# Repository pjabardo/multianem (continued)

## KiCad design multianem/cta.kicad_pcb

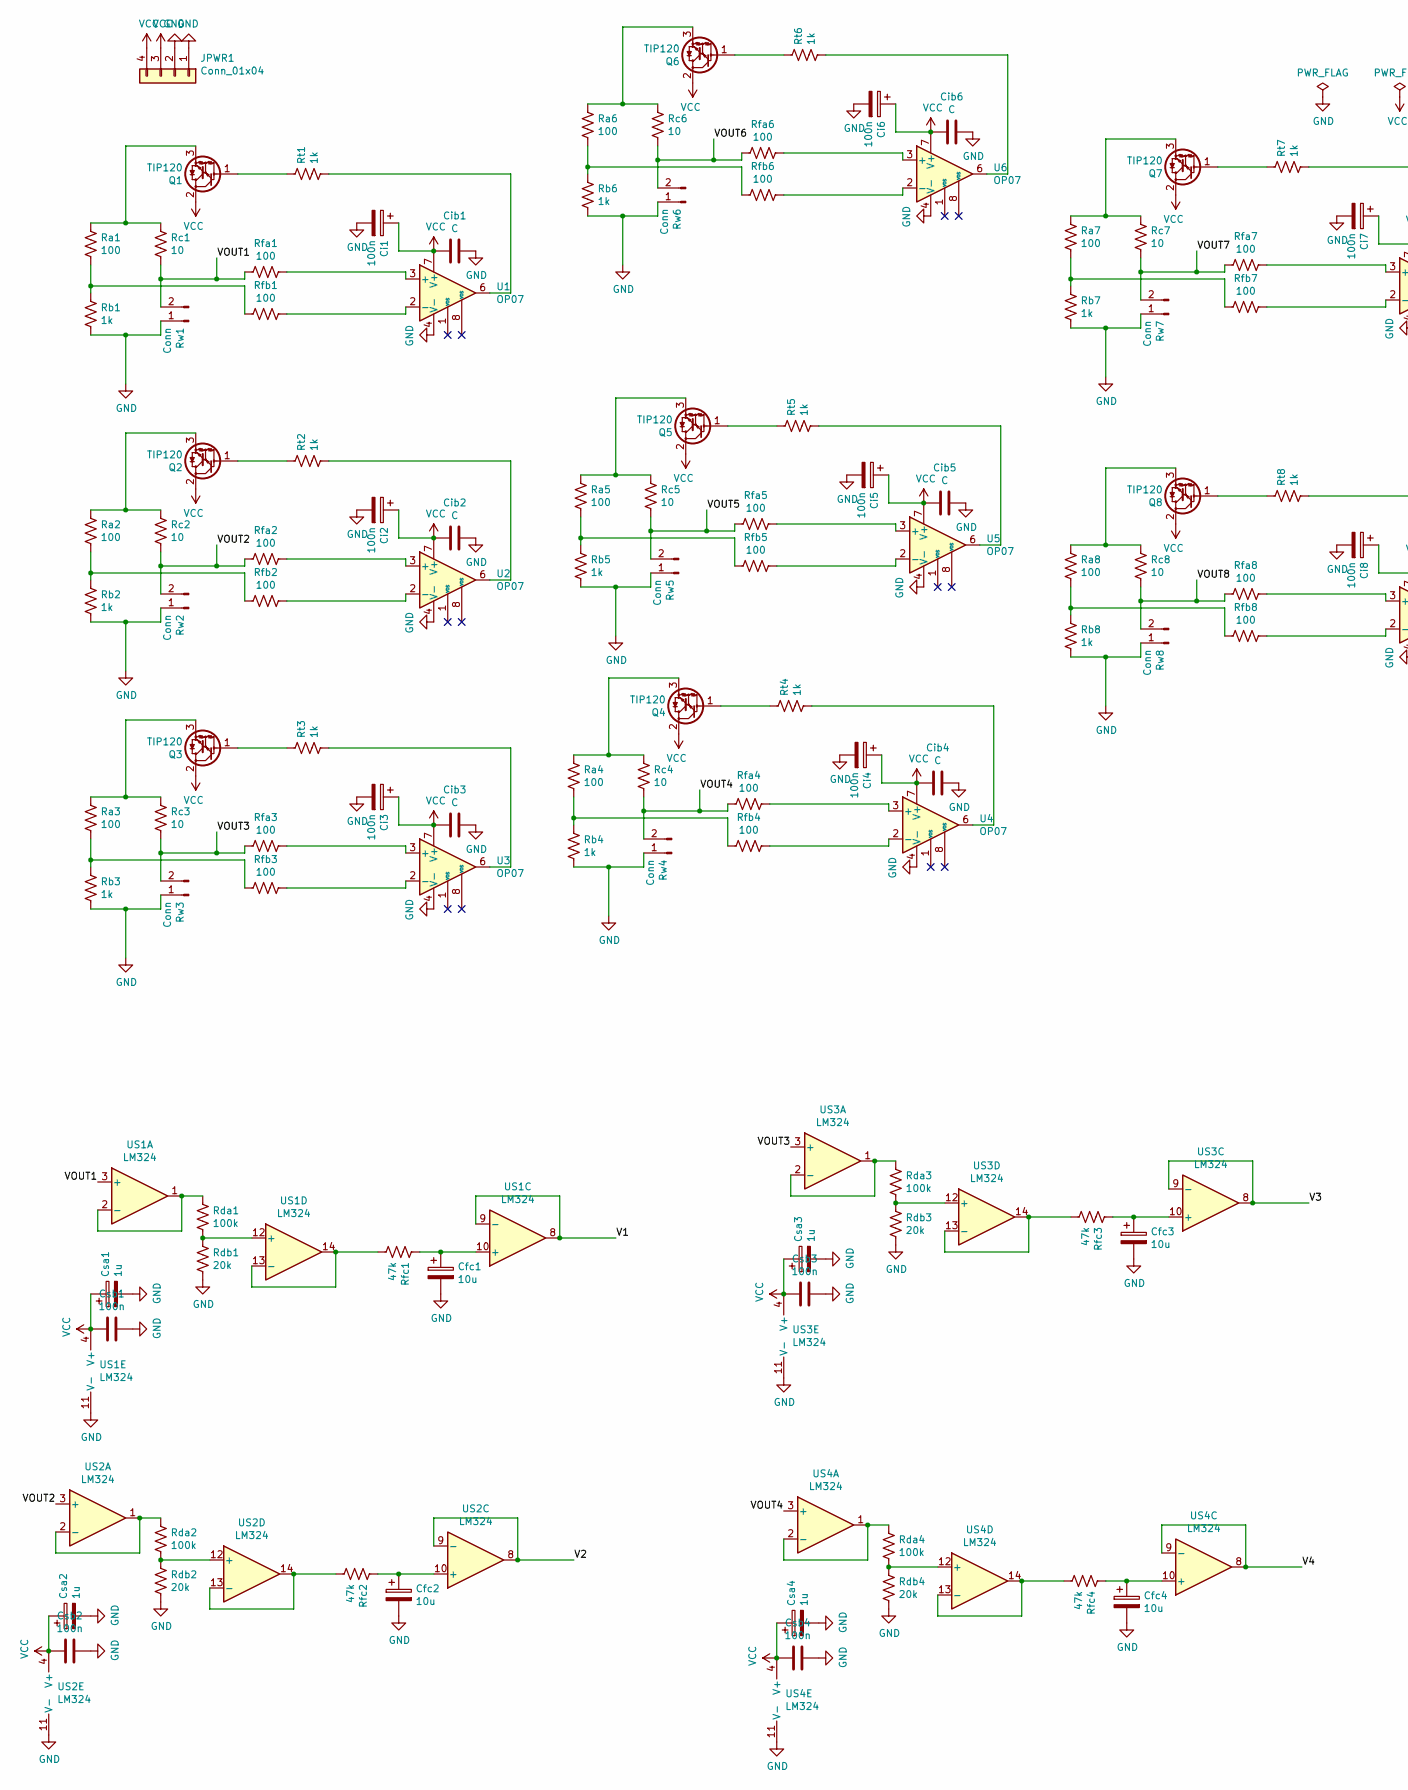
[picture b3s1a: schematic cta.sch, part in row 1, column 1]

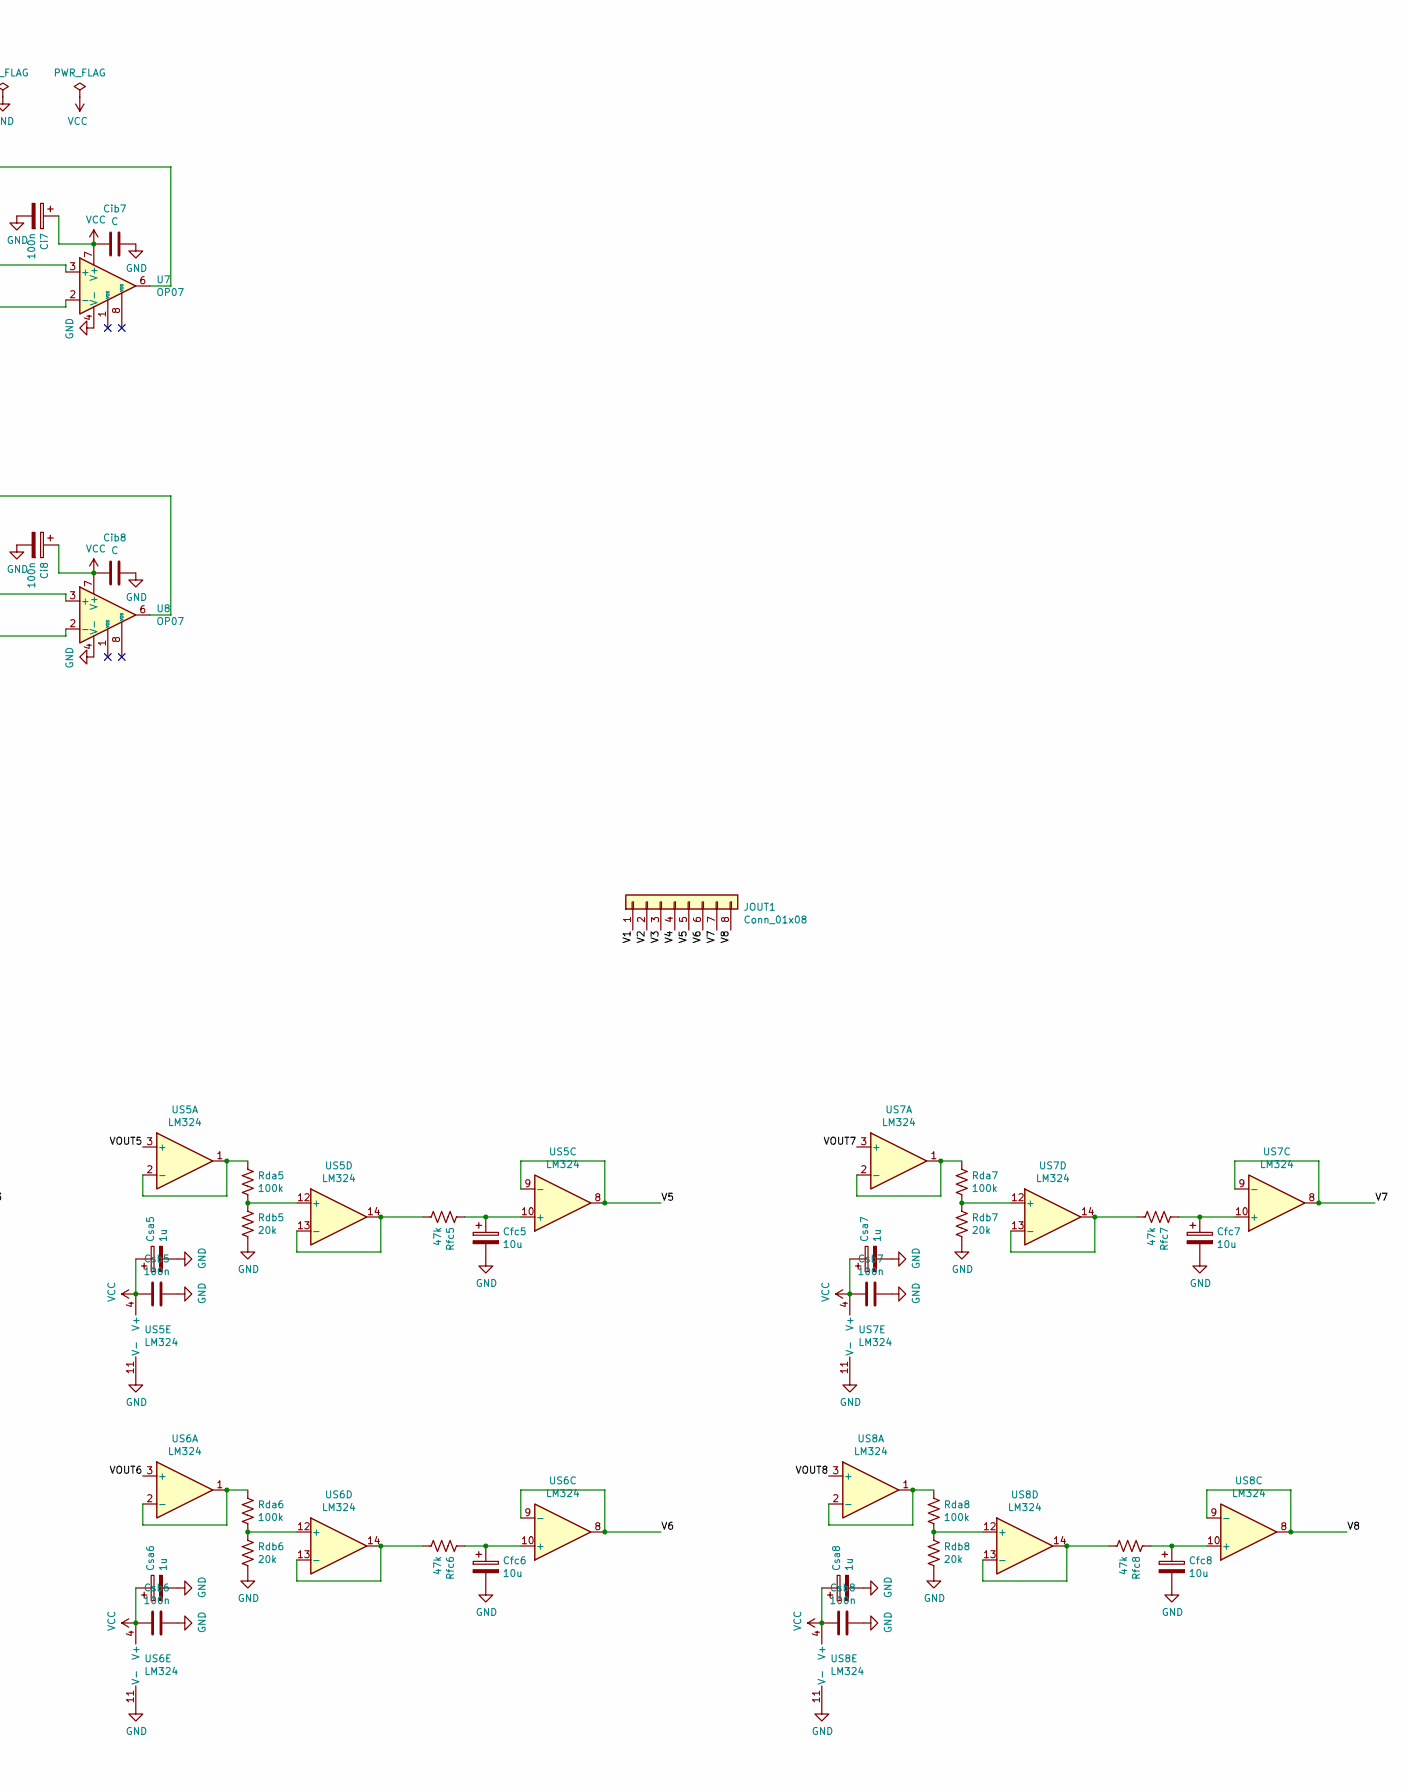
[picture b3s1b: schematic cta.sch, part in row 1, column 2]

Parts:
Cfc1, Cfc2, Cfc3, Cfc4, Cfc5, Cfc6, Cfc7, Cfc8: 10u; CP_Radial_D4.0mm_P2.00mm
Ci1, Ci2, Ci3, Ci4, Ci5, Ci6, Ci7, Ci8: 100n; CP_Radial_D4.0mm_P2.00mm
Cib1, Cib2, Cib3, Cib4, Cib5, Cib6, Cib7, Cib8: C; C_Disc_D5.0mm_W2.5mm_P5.00mm
Csa1, Csa2, Csa3, Csa4, Csa5, Csa6, Csa7, Csa8: 1u; CP_Radial_D4.0mm_P2.00mm
Csb1, Csb2, Csb3, Csb4, Csb5, Csb6, Csb7, Csb8: 100n; C_Disc_D5.0mm_W2.5mm_P5.00mm
JOUT1: Conn_01x08; PinHeader_1x08_P2.54mm_Vertical
JPWR1: Conn_01x04; TerminalBlock_bornier-4_P5.08mm
Q1, Q2, Q3, Q4, Q5, Q6, Q7, Q8: TIP120; TO-220-3_Vertical
Ra1, Ra2, Ra3, Ra4, Ra5, Ra6, Ra7, Ra8: 100; R_Axial_DIN0207_L6.3mm_D2.5mm_P10.16mm_Horizontal
Rb1, Rb2, Rb3, Rb4, Rb5, Rb6, Rb7, Rb8: 1k; R_Axial_DIN0207_L6.3mm_D2.5mm_P10.16mm_Horizontal
Rc1, Rc2, Rc3, Rc4, Rc5, Rc6, Rc7, Rc8: 10; R_Axial_Power_L20.0mm_W6.4mm_P22.40mm
Rda1, Rda2, Rda3, Rda4, Rda5, Rda6, Rda7, Rda8: 100k; R_Axial_DIN0207_L6.3mm_D2.5mm_P10.16mm_Horizontal
Rdb1, Rdb2, Rdb3, Rdb4, Rdb5, Rdb6, Rdb7, Rdb8: 20k; R_Axial_DIN0207_L6.3mm_D2.5mm_P10.16mm_Horizontal
Rfa1, Rfa2, Rfa3, Rfa4, Rfa5, Rfa6, Rfa7, Rfa8: 100; R_Axial_DIN0207_L6.3mm_D2.5mm_P10.16mm_Horizontal
Rfb1, Rfb2, Rfb3, Rfb4, Rfb5, Rfb6, Rfb7, Rfb8: 100; R_Axial_DIN0207_L6.3mm_D2.5mm_P10.16mm_Horizontal
Rfc1, Rfc2, Rfc3, Rfc4, Rfc5, Rfc6, Rfc7, Rfc8: 47k; R_Axial_DIN0207_L6.3mm_D2.5mm_P10.16mm_Horizontal
Rt1, Rt2, Rt3, Rt4, Rt5, Rt6, Rt7, Rt8: 1k; R_Axial_DIN0207_L6.3mm_D2.5mm_P10.16mm_Horizontal
Rw1, Rw2, Rw3, Rw4, Rw5, Rw6, Rw7, Rw8: Conn; TerminalBlock_bornier-2_P5.08mm
U1, U2, U3, U4, U5, U6, U7, U8: OP07; DIP-8_W7.62mm_Socket_LongPads
US1, US2, US3, US4, US5, US6, US7, US8: LM324; DIP-14_W7.62mm_LongPads

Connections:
/V1: JOUT1.1, US1.8, US1.9 (-)
/V2: JOUT1.2, US2.8, US2.9 (-)
/V3: JOUT1.3, US3.8, US3.9 (-)
/V4: JOUT1.4, US4.8, US4.9 (-)
/V5: JOUT1.5, US5.8, US5.9 (-)
/V6: JOUT1.6, US6.8, US6.9 (-)
/V7: JOUT1.7, US7.8, US7.9 (-)
/V8: JOUT1.8, US8.8, US8.9 (-)
/VOUT1: Rc1.2, Rfa1.2, Rw1.2, US1.3 (+)
/VOUT2: Rc2.2, Rfa2.2, Rw2.2, US2.3 (+)
/VOUT3: Rc3.2, Rfa3.2, Rw3.2, US3.3 (+)
/VOUT4: Rc4.2, Rfa4.2, Rw4.2, US4.3 (+)
/VOUT5: Rc5.2, Rfa5.2, Rw5.2, US5.3 (+)
/VOUT6: Rc6.2, Rfa6.2, Rw6.2, US6.3 (+)
/VOUT7: Rc7.2, Rfa7.2, Rw7.2, US7.3 (+)
/VOUT8: Rc8.2, Rfa8.2, Rw8.2, US8.3 (+)
GND: Cfc1.2, Cfc2.2, Cfc3.2, Cfc4.2, Cfc5.2, Cfc6.2, Cfc7.2, Cfc8.2, Ci1.2, Ci2.2, Ci3.2, Ci4.2, Ci5.2, Ci6.2, Ci7.2, Ci8.2, Cib1.1, Cib2.1, Cib3.1, Cib4.1, Cib5.1, Cib6.1, Cib7.1, Cib8.1, Csa1.2, Csa2.2, Csa3.2, Csa4.2, Csa5.2, Csa6.2, Csa7.2, Csa8.2, Csb1.1, Csb2.1, Csb3.1, Csb4.1, Csb5.1, Csb6.1, Csb7.1, Csb8.1, JPWR1.1, JPWR1.2, Rb1.2, Rb2.2, Rb3.2, Rb4.2, Rb5.2, Rb6.2, Rb7.2, Rb8.2, Rdb1.2, Rdb2.2, Rdb3.2, Rdb4.2, Rdb5.2, Rdb6.2, Rdb7.2, Rdb8.2, Rw1.1, Rw2.1, Rw3.1, Rw4.1, Rw5.1, Rw6.1, Rw7.1, Rw8.1, U1.4 (V-), U2.4 (V-), U3.4 (V-), U4.4 (V-), U5.4 (V-), U6.4 (V-), U7.4 (V-), U8.4 (V-), US1.11 (V-), US2.11 (V-), US3.11 (V-), US4.11 (V-), US5.11 (V-), US6.11 (V-), US7.11 (V-), US8.11 (V-)
unnamed: Cfc1.1, Rfc1.1, US1.10 (+)
unnamed: Cfc2.1, Rfc2.1, US2.10 (+)
unnamed: Cfc3.1, Rfc3.1, US3.10 (+)
unnamed: Cfc4.1, Rfc4.1, US4.10 (+)
unnamed: Cfc5.1, Rfc5.1, US5.10 (+)
unnamed: Cfc6.1, Rfc6.1, US6.10 (+)
unnamed: Cfc7.1, Rfc7.1, US7.10 (+)
unnamed: Cfc8.1, Rfc8.1, US8.10 (+)
unnamed: Q1.1 (B), Rt1.1
unnamed: Q1.3 (E), Ra1.1, Rc1.1
unnamed: Q2.1 (B), Rt2.1
unnamed: Q2.3 (E), Ra2.1, Rc2.1
unnamed: Q3.1 (B), Rt3.1
unnamed: Q3.3 (E), Ra3.1, Rc3.1
unnamed: Q4.1 (B), Rt4.1
unnamed: Q4.3 (E), Ra4.1, Rc4.1
unnamed: Q5.1 (B), Rt5.1
unnamed: Q5.3 (E), Ra5.1, Rc5.1
unnamed: Q6.1 (B), Rt6.1
unnamed: Q6.3 (E), Ra6.1, Rc6.1
unnamed: Q7.1 (B), Rt7.1
unnamed: Q7.3 (E), Ra7.1, Rc7.1
unnamed: Q8.1 (B), Rt8.1
unnamed: Q8.3 (E), Ra8.1, Rc8.1
unnamed: Ra1.2, Rb1.1, Rfb1.2
unnamed: Ra2.2, Rb2.1, Rfb2.2
unnamed: Ra3.2, Rb3.1, Rfb3.2
unnamed: Ra4.2, Rb4.1, Rfb4.2
unnamed: Ra5.2, Rb5.1, Rfb5.2
unnamed: Ra6.2, Rb6.1, Rfb6.2
unnamed: Ra7.2, Rb7.1, Rfb7.2
unnamed: Ra8.2, Rb8.1, Rfb8.2
unnamed: Rda1.1, US1.1, US1.2 (-)
unnamed: Rda1.2, Rdb1.1, US1.12 (+)
unnamed: Rda2.1, US2.1, US2.2 (-)
unnamed: Rda2.2, Rdb2.1, US2.12 (+)
unnamed: Rda3.1, US3.1, US3.2 (-)
unnamed: Rda3.2, Rdb3.1, US3.12 (+)
unnamed: Rda4.1, US4.1, US4.2 (-)
unnamed: Rda4.2, Rdb4.1, US4.12 (+)
unnamed: Rda5.1, US5.1, US5.2 (-)
unnamed: Rda5.2, Rdb5.1, US5.12 (+)
unnamed: Rda6.1, US6.1, US6.2 (-)
unnamed: Rda6.2, Rdb6.1, US6.12 (+)
unnamed: Rda7.1, US7.1, US7.2 (-)
unnamed: Rda7.2, Rdb7.1, US7.12 (+)
unnamed: Rda8.1, US8.1, US8.2 (-)
unnamed: Rda8.2, Rdb8.1, US8.12 (+)
unnamed: Rfa1.1, U1.3 (+)
unnamed: Rfa2.1, U2.3 (+)
unnamed: Rfa3.1, U3.3 (+)
unnamed: Rfa4.1, U4.3 (+)
unnamed: Rfa5.1, U5.3 (+)
unnamed: Rfa6.1, U6.3 (+)
unnamed: Rfa7.1, U7.3 (+)
unnamed: Rfa8.1, U8.3 (+)
unnamed: Rfb1.1, U1.2 (-)
unnamed: Rfb2.1, U2.2 (-)
unnamed: Rfb3.1, U3.2 (-)
unnamed: Rfb4.1, U4.2 (-)
unnamed: Rfb5.1, U5.2 (-)
unnamed: Rfb6.1, U6.2 (-)
unnamed: Rfb7.1, U7.2 (-)
unnamed: Rfb8.1, U8.2 (-)
unnamed: Rfc1.2, US1.13 (-), US1.14
unnamed: Rfc2.2, US2.13 (-), US2.14
unnamed: Rfc3.2, US3.13 (-), US3.14
unnamed: Rfc4.2, US4.13 (-), US4.14
unnamed: Rfc5.2, US5.13 (-), US5.14
unnamed: Rfc6.2, US6.13 (-), US6.14
unnamed: Rfc7.2, US7.13 (-), US7.14
unnamed: Rfc8.2, US8.13 (-), US8.14
unnamed: Rt1.2, U1.6
unnamed: Rt2.2, U2.6
unnamed: Rt3.2, U3.6
unnamed: Rt4.2, U4.6
unnamed: Rt5.2, U5.6
unnamed: Rt6.2, U6.6
unnamed: Rt7.2, U7.6
unnamed: Rt8.2, U8.6
VCC: Ci1.1, Ci2.1, Ci3.1, Ci4.1, Ci5.1, Ci6.1, Ci7.1, Ci8.1, Cib1.2, Cib2.2, Cib3.2, Cib4.2, Cib5.2, Cib6.2, Cib7.2, Cib8.2, Csa1.1, Csa2.1, Csa3.1, Csa4.1, Csa5.1, Csa6.1, Csa7.1, Csa8.1, Csb1.2, Csb2.2, Csb3.2, Csb4.2, Csb5.2, Csb6.2, Csb7.2, Csb8.2, JPWR1.3, JPWR1.4, Q1.2 (C), Q2.2 (C), Q3.2 (C), Q4.2 (C), Q5.2 (C), Q6.2 (C), Q7.2 (C), Q8.2 (C), U1.7 (V+), U2.7 (V+), U3.7 (V+), U4.7 (V+), U5.7 (V+), U6.7 (V+), U7.7 (V+), U8.7 (V+), US1.4 (V+), US2.4 (V+), US3.4 (V+), US4.4 (V+), US5.4 (V+), US6.4 (V+), US7.4 (V+), US8.4 (V+)

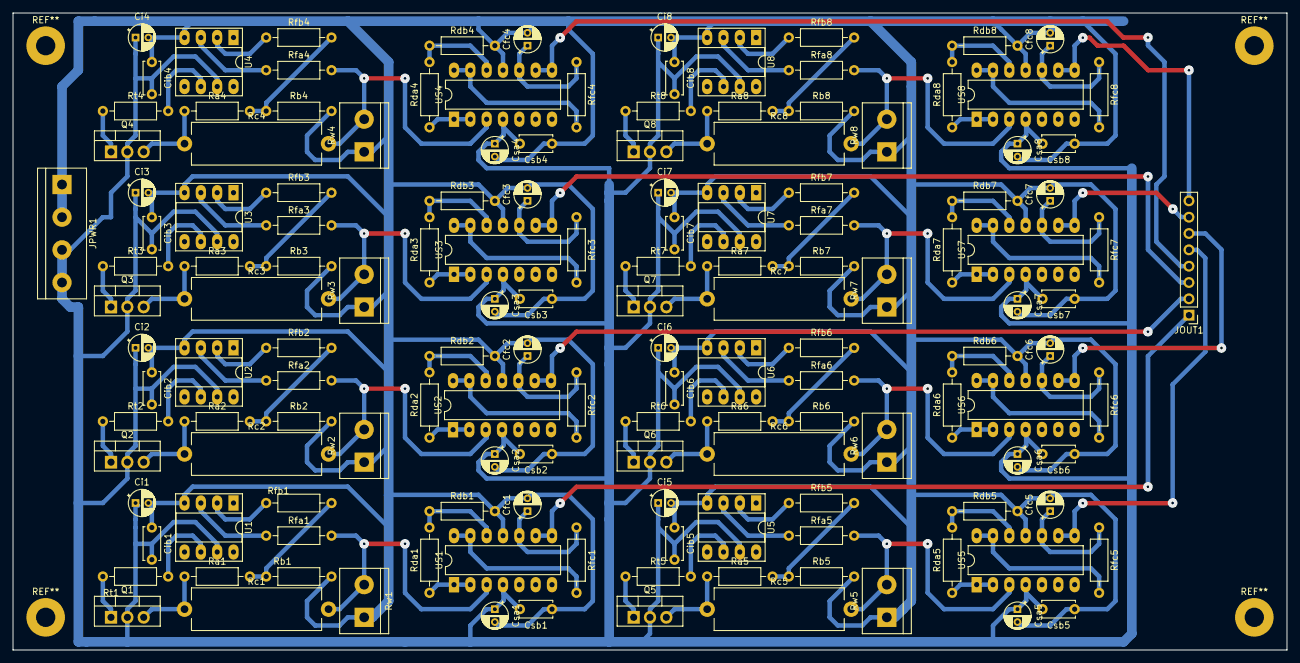
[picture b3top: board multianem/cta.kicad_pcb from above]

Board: 2 copper layers, 198.1 x 99.1 mm, 146 parts (0 on the bottom side), 98 nets.

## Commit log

2021-04-16 Initial commit for the multianem project
2021-04-16 Added other boards to the project.
    I think they will be useful in the future. For now I will just keep them here.
2021-04-16 Working on making the multinanem16 board use symmetric power input.
    This way I can use more types of op-amps.
2021-04-18 Got arduino to read 32 channels!
    Still need to develop an interface. I think I will use the Scanivalve as a template.
2021-04-19 Added more power inputs to the board
    To make it easy to stack the 8 channel boards, added a Vcc and GND inputs.
2021-04-20 Working on adding symmetric power to the multianem16 board.
    Almost done.
2021-04-23 Finnished adding Vee to the 16 anemometers board.
2021-04-23 Improved the multianem16 board
    Moved the power terminal block to the other side of the board.
2021-04-25 Working on new circuit
    Changed TerminalBlock footprint to pin header for thermistor probe.
2021-04-25 Setting up the the board for the on circuit.
    Depending on the offset of the opamp, the circuit will need some help turning on. Getting ready to implement this.
2021-04-29 The multianem16 board is almost ready: need to replace Ron by an diode
    The problem is that with a resistor every single anemometer is coupled to the others. A diode (1n4148) should isolate them.
    The board that I built was kind of poor. Too many flaws in the traces.
2021-05-01 Replaced the Ron? resistors by Don? capacitors
    I tested the original board and it appeared to be working. Let's try this for real!
2021-05-04 Working on the data acquisition part
    I don't know if I will be able to use wifi in the wind tunnel.
2021-05-05 Worked on data acquisition using tghe usb port
    For now a very simple interface is employed. I also wrote a python interface to the board.
    Now I will have to write a XML-RPC server so that the computer can aquire the data. The esp32 will be connected to a raspberry pi and from there through a cabled network to the computer.
2021-05-05 Added a XML-RPC client for the data acquisition
    Module espdaqclient.py implements a python XML-RPC client.
2021-05-06 Small mistake that had problems compiling depending on arduino version
    char* -> uint8_t*
2021-05-20 Started working on 8 anemometer board
    The 16 anemometer board is working. But I think that 16 is too much. It would be better to use 8 anemometers per board.
    The experience in building and using the multianem16 board and the esp32-daq-board showed some flaws in the design. Not related to the electronic circuit.
    The following problems were observed:
    * Large current. For 32 anemometers, more than 3 A was observed. With a board with 8 anemometers, a current of 1 A per board would be sufficient.
    * More flexible usage.
    * Need to design a multi-temperature board.
2021-05-20 Created the multiname8 board
    I recycled the multinam16 board and the numbering of each anemometer's component is 1-4 and 9-12. I might (might...) change the numbering 9-12 to 5-8. The output is also inverted inthe flat cable com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
2021-06-04 Major changes in the esp daq board.
    Now the analog ground is given in a ninth wire for each board in the same flat cable.
    Power supply will be from the ESP board.
2021-06-05 Added a terminal block to esp32-daq-board
    This terminal exposes the 5V supply, reference voltage and ground. This makes it easier to adjust the the reference voltage.
2021-06-05 Moved the box to the corresponding printer3d folder
2021-06-05 Created 3d printed parts for the box
    For now only the bottom plates and lateral plates where BNC connectors go has been drawn.
2021-06-16 Created gerber files for fabrication
    I will try to build the board on some fab.
2021-06-16 Unifying all the grounds AGND and DGND
    On the previous version, each anemometer had a ground that was connected to the AGND present in the MCP3208. This was burning the MCP3208. I still need to undersant how to work with this AGND properl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
2021-06-20 Fixing a few things on the python daq code
2021-06-29 Gerber files for multianem8 and started working on ctaflex
    Sent the gerber files to JLCPCB to manufacture the multianem8 boards.
    Started working on ctaflex, a single anemometer circuit very flexible for testing different types of thermistors and allowing the accurate measurement of resistance.
2022-06-01 Added numbers to the lateral pannels
    Now we one pannel for the right hand side (1-4) and one for the left (5-8).
2023-04-10 Simplified programming a little bit
    Now there is a very long timeout. Things appear to be working but it is not very accepting of errors.
2023-04-23 Created module hotwire.py
    This module deals with calculating velocities and handling anemometer
    calibration.
    The notebook `hotwire-example.ipynb` has a simple example using the module.
2023-11-22 Implemented a templated class for controlling data acquisition
    For now I've tested only serial communications. I should also implement the WiFi version.
2023-11-22 WiFi appears to be working!
    Now write the high level language interface!
2023-11-22 Using serial communications for now
    I still don't know how to stop data acquisition via software. Perhaps using
    WiFi this is easier.
2023-11-23 Added status and reopen command in python code
    Just to better sort out codes
